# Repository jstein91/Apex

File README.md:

# Apex
 APEX KEYBOARD

TKL keyboard with OLED, USB-C, USB hub and encoder.

## Inspiration

I thought of this board as a way to get all the features I want in a keyboard (encoders, OLED, USB hub) but with a design I can evolve with the times and add features to as my skills and knowledge increase. At its core, I intend for it to be a daily driver that I will be able to use for many years and one that I can use and redesign as new tech comes out. The diging borrows heavily from the hub keyboard created by /konstantinwerner and has obvious inspiration from the ever-sought-after Satisfaction 75.

To that end, as a base design the keyboard utilizes the unified USB C daughter board designed by Acheron Project, has an OLED, a rotary encoder, and an integrated USB hub with 2 USB A ports. 

I know that this desgin isnt perfect. I plan to refine the key matrix. I also intend to implement various design changes in the future iterations such as:
 - RGB underglow
 - Per key backlighting
 - Design USB A daughterboard to make hub swappable between USB A and USB C
 - Possible bluetooth
 - Implement pogo pin for wireless communication between keyboard and seperate numpad(TBD) (much more research needed)

## Reference:

https://github.com/ruiqimao/keyboard-pcb-guide

http://blog.komar.be/how-to-make-a-keyboard-the-matrix/?source=post_page---------------------------

https://wiki.ai03.com/books/pcb-design

http://builder.swillkb.com/

## Resources:

https://github.com/CaninoDev/MechanicalKeyboardKiCADTemplates

https://github.com/konstantinwerner/hub_keyboard

https://github.com/BenRoe/awesome-mechanical-keyboard

https://github.com/di0ib/Misc

https://github.com/CaninoDev/MechanicalKeyboardKiCADTemplates

http://ww1.microchip.com/downloads/en/DeviceDoc/doc7593.pdf

https://kb.xyz.is/

https://builder.mrkeebs.com/

https://github.com/adamws/kicad-kbplacer

https://github.com/AcheronProject

https://github.com/ai03-2725/Unified-Daughterboard

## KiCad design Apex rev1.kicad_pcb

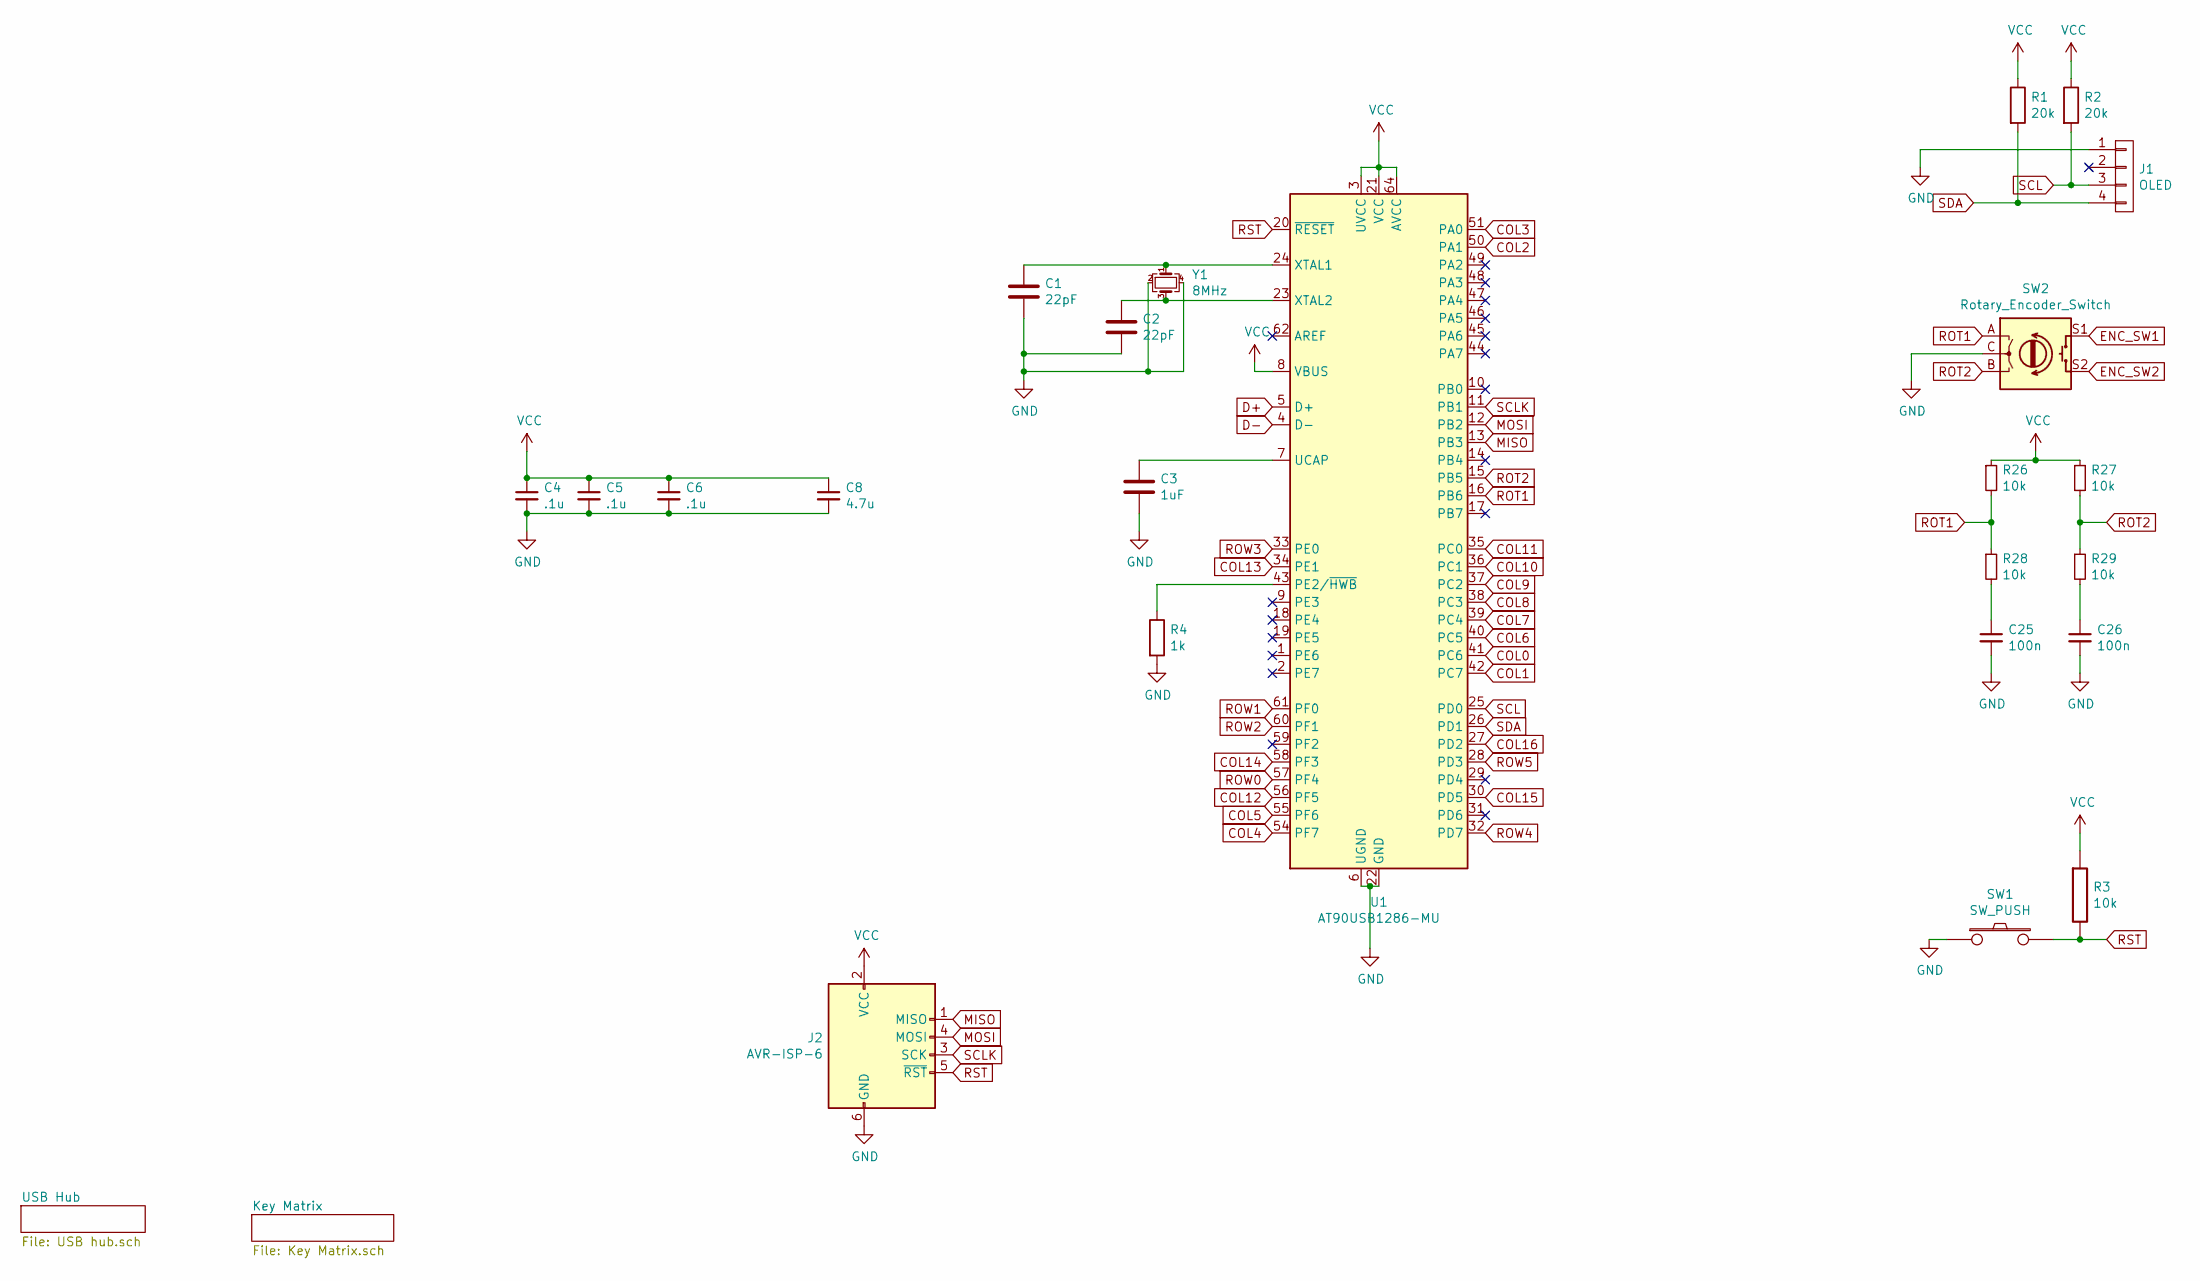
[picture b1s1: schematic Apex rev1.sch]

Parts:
C1, C2: 22pF; C_0805_2012Metric
C3: 1uF; C_0805_2012Metric
C4, C5, C6: .1u; C_0805_2012Metric
C8: 4.7u; C_0805_2012Metric
C25, C26: 100n; C_0805_2012Metric
J1: OLED; 128X32_I2C_OLED
J2: AVR-ISP-6; ICSP-Header
R1, R2: 20k; R_0603
R3, R26, R27, R28, R29: 10k; R_0603
R4: 1k; R_0603
SW1: SW_PUSH; SKQG-1155865
SW2: Rotary_Encoder_Switch; RotaryEncoder_EC11
U1: AT90USB1286-MU; QFN-64-1EP_9x9mm_P0.5mm_EP7.5x7.5mm
Y1: 8MHz; Crystal_SMD_3225-4Pin_3.2x2.5mm

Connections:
COL0: U1.41 (PC6); also elsewhere on the board
COL1: U1.42 (PC7); also elsewhere on the board
COL2: U1.50 (PA1); also elsewhere on the board
COL3: U1.51 (PA0); also elsewhere on the board
COL4: U1.54 (PF7); also elsewhere on the board
COL5: U1.55 (PF6); also elsewhere on the board
COL6: U1.40 (PC5); also elsewhere on the board
COL7: U1.39 (PC4); also elsewhere on the board
COL8: U1.38 (PC3); also elsewhere on the board
COL9: U1.37 (PC2); also elsewhere on the board
COL10: U1.36 (PC1); also elsewhere on the board
COL11: U1.35 (PC0); also elsewhere on the board
COL12: U1.56 (PF5); also elsewhere on the board
COL13: U1.34 (PE1); also elsewhere on the board
COL14: U1.58 (PF3); also elsewhere on the board
COL15: U1.30 (PD5); also elsewhere on the board
COL16: U1.27 (PD2); also elsewhere on the board
D+: U1.5 (D+); also elsewhere on the board
D-: U1.4 (D-); also elsewhere on the board
ENC_SW1: SW2.S1
ENC_SW2: SW2.S2
GND: C1.2, C2.2, C3.2, C4.2, C5.2, C6.2, C8.2, C25.2, C26.2, J1.1, J2.6 (GND), R4.2, SW1.1, SW2.C, U1.6 (UGND), U1.22 (GND), U1.53 (GND), U1.63 (GND), U1.65 (GND), Y1.2, Y1.4; also elsewhere on the board
MISO: J2.1 (MISO), U1.13 (PB3)
MOSI: J2.4 (MOSI), U1.12 (PB2)
unnamed: C1.1, U1.24 (XTAL1), Y1.1
unnamed: C2.1, U1.23 (XTAL2), Y1.3
unnamed: C3.1, U1.7 (UCAP)
unnamed: C25.1, R28.2
unnamed: C26.1, R29.2
unnamed: R4.1, U1.43 (PE2/~HWB)
ROT1: R26.2, R28.1, SW2.A, U1.16 (PB6)
ROT2: R27.2, R29.1, SW2.B, U1.15 (PB5)
ROW0: U1.57 (PF4); also elsewhere on the board
ROW1: U1.61 (PF0); also elsewhere on the board
ROW2: U1.60 (PF1); also elsewhere on the board
ROW3: U1.33 (PE0); also elsewhere on the board
ROW4: U1.32 (PD7); also elsewhere on the board
ROW5: U1.28 (PD3); also elsewhere on the board
RST: J2.5 (~RST), R3.2, SW1.2, U1.20 (~RESET)
SCL: J1.3, R2.2, U1.25 (PD0)
SCLK: J2.3 (SCK), U1.11 (PB1)
SDA: J1.4, R1.2, U1.26 (PD1)
VCC: C4.1, C5.1, C6.1, C8.1, J2.2 (VCC), R1.1, R2.1, R3.1, R26.1, R27.1, U1.3 (UVCC), U1.8 (VBUS), U1.21 (VCC), U1.52 (VCC), U1.64 (AVCC); also elsewhere on the board

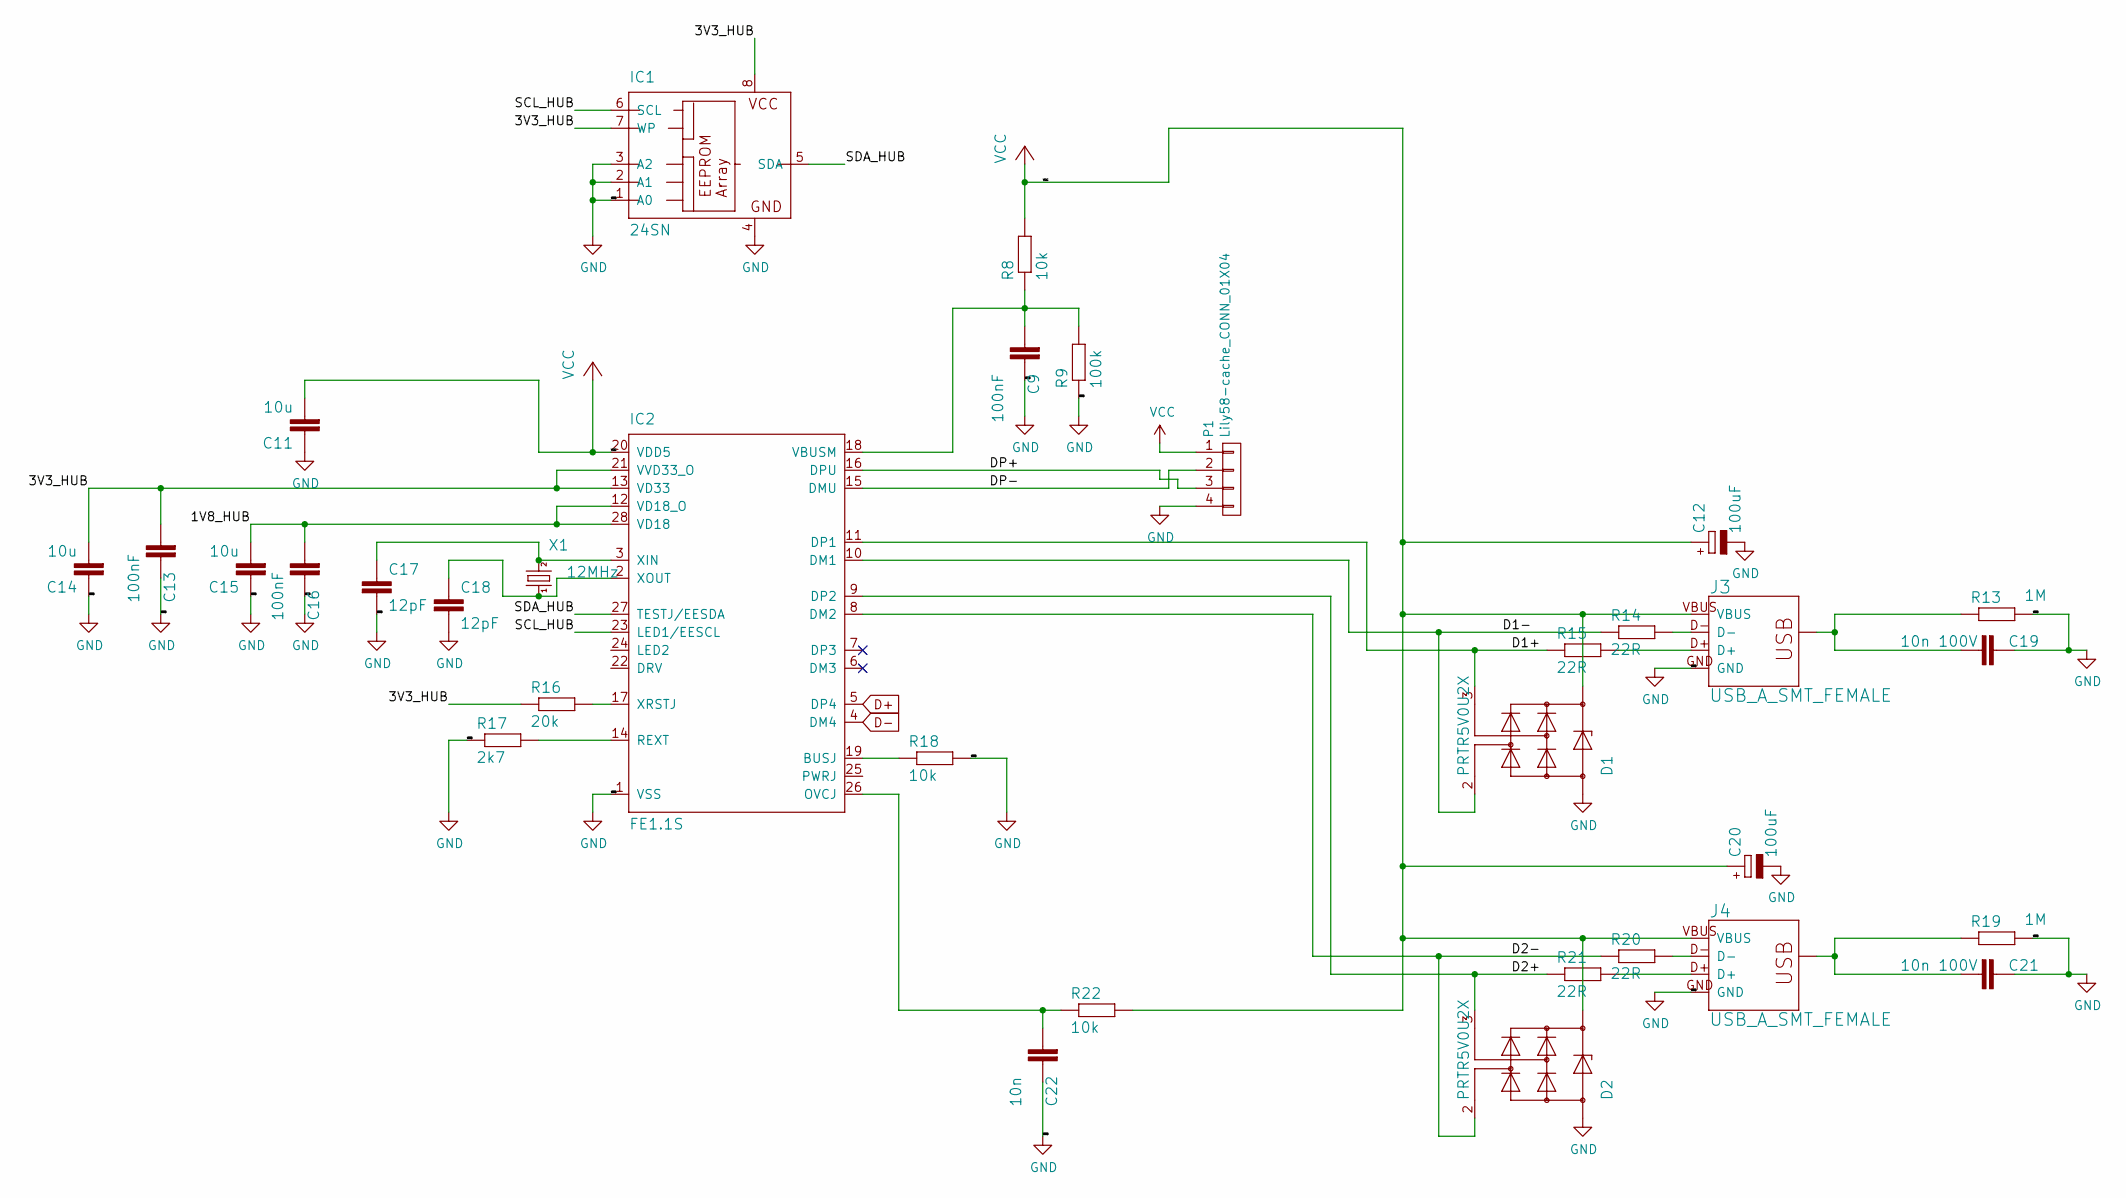
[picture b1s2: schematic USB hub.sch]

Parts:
C9, C13, C16: 100nF; C_0805_2012Metric; LCSC C14663
C11, C14, C15: 10u; C_0805_2012Metric; LCSC C19702
C12, C20: 100uF; CT3528; LCSC C16133
C17, C18: 12pF; C_0805_2012Metric; LCSC C38523
C19, C21: 10n 100V; C_0805_2012Metric; LCSC C84709
C22: 10n; C_0805_2012Metric; LCSC C57112
D1, D2: PRTR5V0U2X; SOT143; DIGIKEY 1727-3884-1-ND
IC1: 24SN; SO-08; LCSC C184083
IC2: FE1.1S; SSOP28; LCSC C9359
J3, J4: USB_A_SMT_FEMALE; USB-A-S-SILK-FEMALE; DIGIKEY 609-4946-1-ND
P1: Lily58-cache_CONN_01X04; JST-SR-4
R8, R18, R22: 10k; R_0603; LCSC C25804
R9: 100k; R_0603; LCSC C25803
R13, R19: 1M; R_0603; LCSC C22935
R14, R15, R20, R21: 22R; R_0603; LCSC C23345
R16: 20k; R_0603; LCSC C4184
R17: 2k7; R_0603; LCSC C13167
X1: 12MHz; Crystal_SMD_3225-4Pin_3.2x2.5mm; LCSC C9002

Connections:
/USB Hub/1V8_HUB: C15.2, C16.2, IC2.12 (VD18_O), IC2.28 (VD18)
/USB Hub/3V3_HUB: C13.2, C14.2, IC1.7 (WP), IC1.8 (VCC), IC2.13 (VD33), IC2.21 (VVD33_O), R16.1
/USB Hub/D1+: D1.3 (IO2), IC2.11 (DP1), R15.1
/USB Hub/D1-: D1.2 (IO1), IC2.10 (DM1), R14.1
/USB Hub/D2+: D2.3 (IO2), IC2.9 (DP2), R21.1
/USB Hub/D2-: D2.2 (IO1), IC2.8 (DM2), R20.1
/USB Hub/DP+: IC2.16 (DPU), P1.3
/USB Hub/DP-: IC2.15 (DMU), P1.2
/USB Hub/SCL_HUB: IC1.6 (SCL), IC2.23 (LED1/EESCL)
/USB Hub/SDA_HUB: IC1.5 (SDA), IC2.27 (TESTJ/EESDA)
D+: IC2.5 (DP4); also elsewhere on the board
D-: IC2.4 (DM4); also elsewhere on the board
GND: C9.1, C11.1, C12.-, C13.1, C14.1, C15.1, C16.1, C17.2, C18.2, C19.1, C20.-, C21.1, C22.1, D1.1 (GND), D2.1 (GND), IC1.1 (A0), IC1.2 (A1), IC1.3 (A2), IC1.4 (GND), IC2.1 (VSS), J3.GND, J4.GND, P1.4, R9.1, R13.2, R17.1, R18.2, R19.2; also elsewhere on the board
unnamed: C9.2, IC2.18 (VBUSM), R8.1, R9.2
unnamed: C17.1, IC2.3 (XIN), X1.3 (2)
unnamed: C18.1, IC2.2 (XOUT), X1.1
unnamed: C19.2, J3.SHLD1 (SHIELD), J3.SHLD2 (SHIELD), R13.1
unnamed: C21.2, J4.SHLD1 (SHIELD), J4.SHLD2 (SHIELD), R19.1
unnamed: C22.2, IC2.26 (OVCJ), R22.1
unnamed: IC2.14 (REXT), R17.2
unnamed: IC2.17 (XRSTJ), R16.2
unnamed: IC2.19 (BUSJ), R18.1
unnamed: J3.D+, R15.2
unnamed: J3.D-, R14.2
unnamed: J4.D+, R21.2
unnamed: J4.D-, R20.2
VCC: C11.2, C12.+, C20.+, D1.4 (VCC), D2.4 (VCC), IC2.20 (VDD5), J3.VBUS, J4.VBUS, P1.1, R8.2, R22.2; also elsewhere on the board

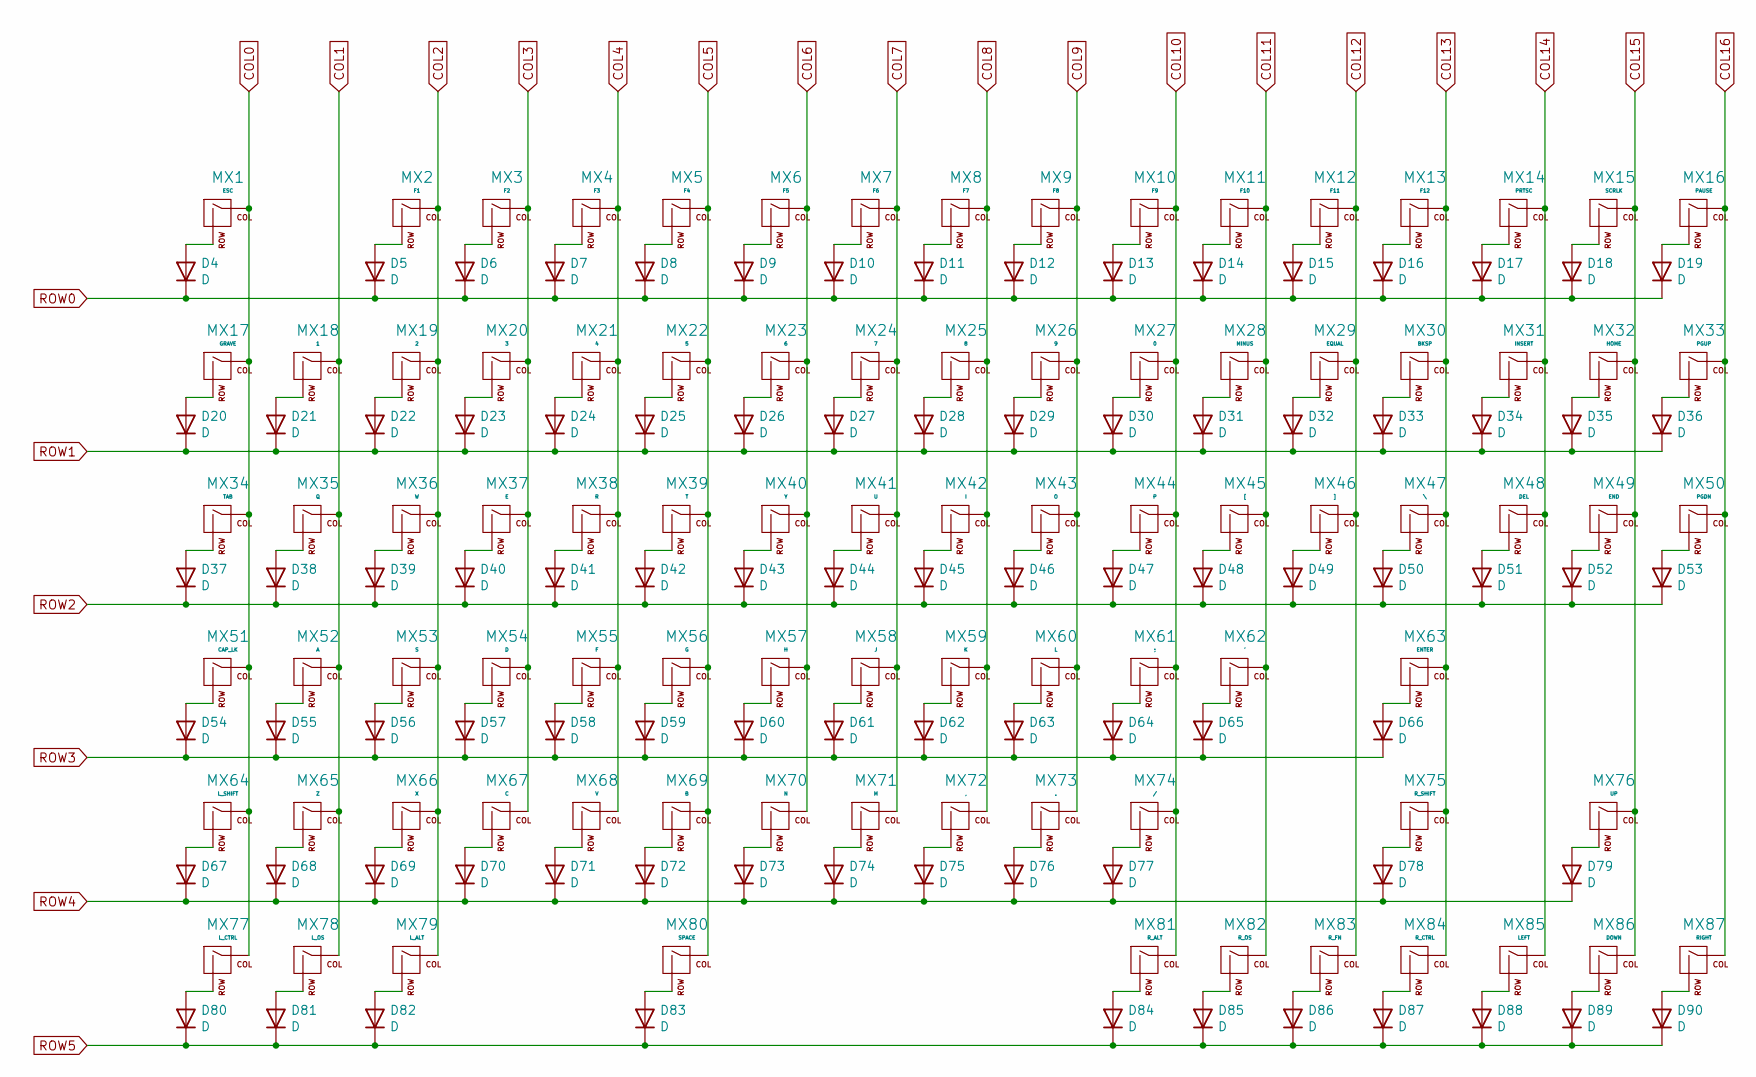
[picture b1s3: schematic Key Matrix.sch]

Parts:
D4, D5, D6, D7, D8, D9, D10, D11, D12, D13, D14, D15, D16, D17, D18, D19, D20, D21, D22, D23, D24, D25, D26, D27, D28, D29, D30, D31, D32, D33, D34, D35, D36, D37, D38, D39, D40, D41, D42, D43, D44, D45, D46, D47, D48, D49, D50, D51, D52, D53, D54, D55, D56, D57, D58, D59, D60, D61, D62, D63, D64, D65, D66, D67, D68, D69, D70, D71, D72, D73, D74, D75, D76, D77, D78, D79, D80, D81, D82, D83, D84, D85, D86, D87, D88, D89, D90: D; D_SOD-123
MX1: ESC; MXOnly-1U-NoLED
MX2: F1; MXOnly-1U-NoLED
MX3: F2; MXOnly-1U-NoLED
MX4: F3; MXOnly-1U-NoLED
MX5: F4; MXOnly-1U-NoLED
MX6: F5; MXOnly-1U-NoLED
MX7: F6; MXOnly-1U-NoLED
MX8: F7; MXOnly-1U-NoLED
MX9: F8; MXOnly-1U-NoLED
MX10: F9; MXOnly-1U-NoLED
MX11: F10; MXOnly-1U-NoLED
MX12: F11; MXOnly-1U-NoLED
MX13: F12; MXOnly-1U-NoLED
MX14: PRTSC; MXOnly-1U-NoLED
MX15: SCRLK; MXOnly-1U-NoLED
MX16: PAUSE; MXOnly-1U-NoLED
MX17: GRAVE; MXOnly-1U-NoLED
MX18: 1; MXOnly-1U-NoLED
MX19: 2; MXOnly-1U-NoLED
MX20: 3; MXOnly-1U-NoLED
MX21: 4; MXOnly-1U-NoLED
MX22: 5; MXOnly-1U-NoLED
MX23: 6; MXOnly-1U-NoLED
MX24: 7; MXOnly-1U-NoLED
MX25: 8; MXOnly-1U-NoLED
MX26: 9; MXOnly-1U-NoLED
MX27: 0; MXOnly-1U-NoLED
MX28: MINUS; MXOnly-1U-NoLED
MX29: EQUAL; MXOnly-1U-NoLED
MX30: BKSP; MXOnly-2U-NoLED
MX31: INSERT; MXOnly-1U-NoLED
MX32: HOME; MXOnly-1U-NoLED
MX33: PGUP; MXOnly-1U-NoLED
MX34: TAB; MXOnly-1.5U-NoLED
MX35: Q; MXOnly-1U-NoLED
MX36: W; MXOnly-1U-NoLED
MX37: E; MXOnly-1U-NoLED
MX38: R; MXOnly-1U-NoLED
MX39: T; MXOnly-1U-NoLED
MX40: Y; MXOnly-1U-NoLED
MX41: U; MXOnly-1U-NoLED
MX42: I; MXOnly-1U-NoLED
MX43: O; MXOnly-1U-NoLED
MX44: P; MXOnly-1U-NoLED
MX45: [; MXOnly-1U-NoLED
MX46: ]; MXOnly-1U-NoLED
MX47: \\; MXOnly-1.5U-NoLED
MX48: DEL; MXOnly-1U-NoLED
MX49: END; MXOnly-1U-NoLED
MX50: PGDN; MXOnly-1U-NoLED
MX51: CAP_LK; MXOnly-1.75U-NoLED
MX52: A; MXOnly-1U-NoLED
MX53: S; MXOnly-1U-NoLED
MX54: D; MXOnly-1U-NoLED
MX55: F; MXOnly-1U-NoLED
MX56: G; MXOnly-1U-NoLED
MX57: H; MXOnly-1U-NoLED
MX58: J; MXOnly-1U-NoLED
MX59: K; MXOnly-1U-NoLED
MX60: L; MXOnly-1U-NoLED
MX61: ;; MXOnly-1U-NoLED
MX62: '; MXOnly-1U-NoLED
MX63: ENTER; MXOnly-2.25U-NoLED
MX64: L_SHIFT; MXOnly-2.25U-NoLED
MX65: Z; MXOnly-1U-NoLED
MX66: X; MXOnly-1U-NoLED
MX67: C; MXOnly-1U-NoLED
MX68: V; MXOnly-1U-NoLED
MX69: B; MXOnly-1U-NoLED
MX70: N; MXOnly-1U-NoLED
MX71: M; MXOnly-1U-NoLED
MX72: ,; MXOnly-1U-NoLED
MX73: .; MXOnly-1U-NoLED
MX74: /; MXOnly-1U-NoLED
MX75: R_SHIFT; MXOnly-2.75U-NoLED
MX76: UP; MXOnly-1U-NoLED
MX77: L_CTRL; MXOnly-1.25U-NoLED
MX78: L_OS; MXOnly-1.25U-NoLED
MX79: L_ALT; MXOnly-1.25U-NoLED
MX80: SPACE; MXOnly-6.25U-NoLED
MX81: R_ALT; MXOnly-1.75U-NoLED
MX82: R_OS; MXOnly-1.25U-NoLED
MX83: R_FN; MXOnly-1.25U-NoLED
MX84: R_CTRL; MXOnly-1.25U-NoLED
MX85: LEFT; MXOnly-1U-NoLED
MX86: DOWN; MXOnly-1U-NoLED
MX87: RIGHT; MXOnly-1U-NoLED

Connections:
COL0: MX1.1 (COL), MX17.1 (COL), MX34.1 (COL), MX51.1 (COL), MX64.1 (COL), MX77.1 (COL); also elsewhere on the board
COL1: MX18.1 (COL), MX35.1 (COL), MX52.1 (COL), MX65.1 (COL), MX78.1 (COL); also elsewhere on the board
COL2: MX2.1 (COL), MX19.1 (COL), MX36.1 (COL), MX53.1 (COL), MX66.1 (COL), MX79.1 (COL); also elsewhere on the board
COL3: MX3.1 (COL), MX20.1 (COL), MX37.1 (COL), MX54.1 (COL), MX67.1 (COL); also elsewhere on the board
COL4: MX4.1 (COL), MX21.1 (COL), MX38.1 (COL), MX55.1 (COL), MX68.1 (COL); also elsewhere on the board
COL5: MX5.1 (COL), MX22.1 (COL), MX39.1 (COL), MX56.1 (COL), MX69.1 (COL), MX80.1 (COL); also elsewhere on the board
COL6: MX6.1 (COL), MX23.1 (COL), MX40.1 (COL), MX57.1 (COL), MX70.1 (COL); also elsewhere on the board
COL7: MX7.1 (COL), MX24.1 (COL), MX41.1 (COL), MX58.1 (COL), MX71.1 (COL); also elsewhere on the board
COL8: MX8.1 (COL), MX25.1 (COL), MX42.1 (COL), MX59.1 (COL), MX72.1 (COL); also elsewhere on the board
COL9: MX9.1 (COL), MX26.1 (COL), MX43.1 (COL), MX60.1 (COL), MX73.1 (COL); also elsewhere on the board
COL10: MX10.1 (COL), MX27.1 (COL), MX44.1 (COL), MX61.1 (COL), MX74.1 (COL), MX81.1 (COL); also elsewhere on the board
COL11: MX11.1 (COL), MX28.1 (COL), MX45.1 (COL), MX62.1 (COL), MX82.1 (COL); also elsewhere on the board
COL12: MX12.1 (COL), MX29.1 (COL), MX46.1 (COL), MX83.1 (COL); also elsewhere on the board
COL13: MX13.1 (COL), MX30.1 (COL), MX47.1 (COL), MX63.1 (COL), MX75.1 (COL), MX84.1 (COL); also elsewhere on the board
COL14: MX14.1 (COL), MX31.1 (COL), MX48.1 (COL), MX85.1 (COL); also elsewhere on the board
COL15: MX15.1 (COL), MX32.1 (COL), MX49.1 (COL), MX76.1 (COL), MX86.1 (COL); also elsewhere on the board
COL16: MX16.1 (COL), MX33.1 (COL), MX50.1 (COL), MX87.1 (COL); also elsewhere on the board
unnamed: D4.2 (A), MX1.2 (ROW)
unnamed: D5.2 (A), MX2.2 (ROW)
unnamed: D6.2 (A), MX3.2 (ROW)
unnamed: D7.2 (A), MX4.2 (ROW)
unnamed: D8.2 (A), MX5.2 (ROW)
unnamed: D9.2 (A), MX6.2 (ROW)
unnamed: D10.2 (A), MX7.2 (ROW)
unnamed: D11.2 (A), MX8.2 (ROW)
unnamed: D12.2 (A), MX9.2 (ROW)
unnamed: D13.2 (A), MX10.2 (ROW)
unnamed: D14.2 (A), MX11.2 (ROW)
unnamed: D15.2 (A), MX12.2 (ROW)
unnamed: D16.2 (A), MX13.2 (ROW)
unnamed: D17.2 (A), MX14.2 (ROW)
unnamed: D18.2 (A), MX15.2 (ROW)
unnamed: D19.2 (A), MX16.2 (ROW)
unnamed: D20.2 (A), MX17.2 (ROW)
unnamed: D21.2 (A), MX18.2 (ROW)
unnamed: D22.2 (A), MX19.2 (ROW)
unnamed: D23.2 (A), MX20.2 (ROW)
unnamed: D24.2 (A), MX21.2 (ROW)
unnamed: D25.2 (A), MX22.2 (ROW)
unnamed: D26.2 (A), MX23.2 (ROW)
unnamed: D27.2 (A), MX24.2 (ROW)
unnamed: D28.2 (A), MX25.2 (ROW)
unnamed: D29.2 (A), MX26.2 (ROW)
unnamed: D30.2 (A), MX27.2 (ROW)
unnamed: D31.2 (A), MX28.2 (ROW)
unnamed: D32.2 (A), MX29.2 (ROW)
unnamed: D33.2 (A), MX30.2 (ROW)
unnamed: D34.2 (A), MX31.2 (ROW)
unnamed: D35.2 (A), MX32.2 (ROW)
unnamed: D36.2 (A), MX33.2 (ROW)
unnamed: D37.2 (A), MX34.2 (ROW)
unnamed: D38.2 (A), MX35.2 (ROW)
unnamed: D39.2 (A), MX36.2 (ROW)
unnamed: D40.2 (A), MX37.2 (ROW)
unnamed: D41.2 (A), MX38.2 (ROW)
unnamed: D42.2 (A), MX39.2 (ROW)
unnamed: D43.2 (A), MX40.2 (ROW)
unnamed: D44.2 (A), MX41.2 (ROW)
unnamed: D45.2 (A), MX42.2 (ROW)
unnamed: D46.2 (A), MX43.2 (ROW)
unnamed: D47.2 (A), MX44.2 (ROW)
unnamed: D48.2 (A), MX45.2 (ROW)
unnamed: D49.2 (A), MX46.2 (ROW)
unnamed: D50.2 (A), MX47.2 (ROW)
unnamed: D51.2 (A), MX48.2 (ROW)
unnamed: D52.2 (A), MX49.2 (ROW)
unnamed: D53.2 (A), MX50.2 (ROW)
unnamed: D54.2 (A), MX51.2 (ROW)
unnamed: D55.2 (A), MX52.2 (ROW)
unnamed: D56.2 (A), MX53.2 (ROW)
unnamed: D57.2 (A), MX54.2 (ROW)
unnamed: D58.2 (A), MX55.2 (ROW)
unnamed: D59.2 (A), MX56.2 (ROW)
unnamed: D60.2 (A), MX57.2 (ROW)
unnamed: D61.2 (A), MX58.2 (ROW)
unnamed: D62.2 (A), MX59.2 (ROW)
unnamed: D63.2 (A), MX60.2 (ROW)
unnamed: D64.2 (A), MX61.2 (ROW)
unnamed: D65.2 (A), MX62.2 (ROW)
unnamed: D66.2 (A), MX63.2 (ROW)
unnamed: D67.2 (A), MX64.2 (ROW)
unnamed: D68.2 (A), MX65.2 (ROW)
unnamed: D69.2 (A), MX66.2 (ROW)
unnamed: D70.2 (A), MX67.2 (ROW)
unnamed: D71.2 (A), MX68.2 (ROW)
unnamed: D72.2 (A), MX69.2 (ROW)
unnamed: D73.2 (A), MX70.2 (ROW)
unnamed: D74.2 (A), MX71.2 (ROW)
unnamed: D75.2 (A), MX72.2 (ROW)
unnamed: D76.2 (A), MX73.2 (ROW)
unnamed: D77.2 (A), MX74.2 (ROW)
unnamed: D78.2 (A), MX75.2 (ROW)
unnamed: D79.2 (A), MX76.2 (ROW)
unnamed: D80.2 (A), MX77.2 (ROW)
unnamed: D81.2 (A), MX78.2 (ROW)
unnamed: D82.2 (A), MX79.2 (ROW)
unnamed: D83.2 (A), MX80.2 (ROW)
unnamed: D84.2 (A), MX81.2 (ROW)
unnamed: D85.2 (A), MX82.2 (ROW)
unnamed: D86.2 (A), MX83.2 (ROW)
unnamed: D87.2 (A), MX84.2 (ROW)
unnamed: D88.2 (A), MX85.2 (ROW)
unnamed: D89.2 (A), MX86.2 (ROW)
unnamed: D90.2 (A), MX87.2 (ROW)
ROW0: D4.1 (K), D5.1 (K), D6.1 (K), D7.1 (K), D8.1 (K), D9.1 (K), D10.1 (K), D11.1 (K), D12.1 (K), D13.1 (K), D14.1 (K), D15.1 (K), D16.1 (K), D17.1 (K), D18.1 (K), D19.1 (K); also elsewhere on the board
ROW1: D20.1 (K), D21.1 (K), D22.1 (K), D23.1 (K), D24.1 (K), D25.1 (K), D26.1 (K), D27.1 (K), D28.1 (K), D29.1 (K), D30.1 (K), D31.1 (K), D32.1 (K), D33.1 (K), D34.1 (K), D35.1 (K), D36.1 (K); also elsewhere on the board
ROW2: D37.1 (K), D38.1 (K), D39.1 (K), D40.1 (K), D41.1 (K), D42.1 (K), D43.1 (K), D44.1 (K), D45.1 (K), D46.1 (K), D47.1 (K), D48.1 (K), D49.1 (K), D50.1 (K), D51.1 (K), D52.1 (K), D53.1 (K); also elsewhere on the board
ROW3: D54.1 (K), D55.1 (K), D56.1 (K), D57.1 (K), D58.1 (K), D59.1 (K), D60.1 (K), D61.1 (K), D62.1 (K), D63.1 (K), D64.1 (K), D65.1 (K), D66.1 (K); also elsewhere on the board
ROW4: D67.1 (K), D68.1 (K), D69.1 (K), D70.1 (K), D71.1 (K), D72.1 (K), D73.1 (K), D74.1 (K), D75.1 (K), D76.1 (K), D77.1 (K), D78.1 (K), D79.1 (K); also elsewhere on the board
ROW5: D80.1 (K), D81.1 (K), D82.1 (K), D83.1 (K), D84.1 (K), D85.1 (K), D86.1 (K), D87.1 (K), D88.1 (K), D89.1 (K), D90.1 (K); also elsewhere on the board

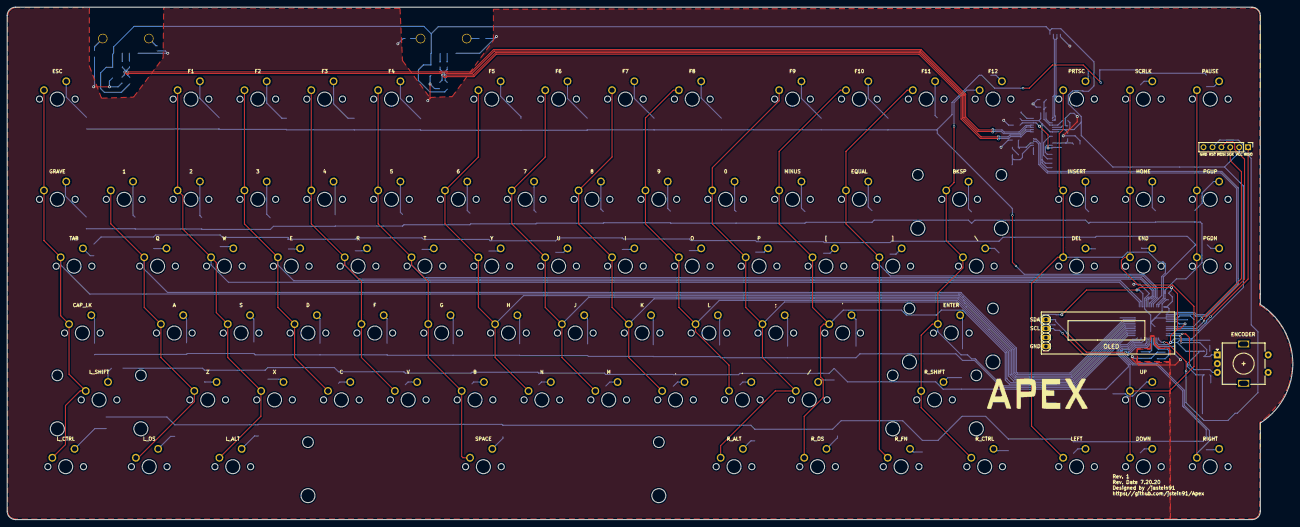
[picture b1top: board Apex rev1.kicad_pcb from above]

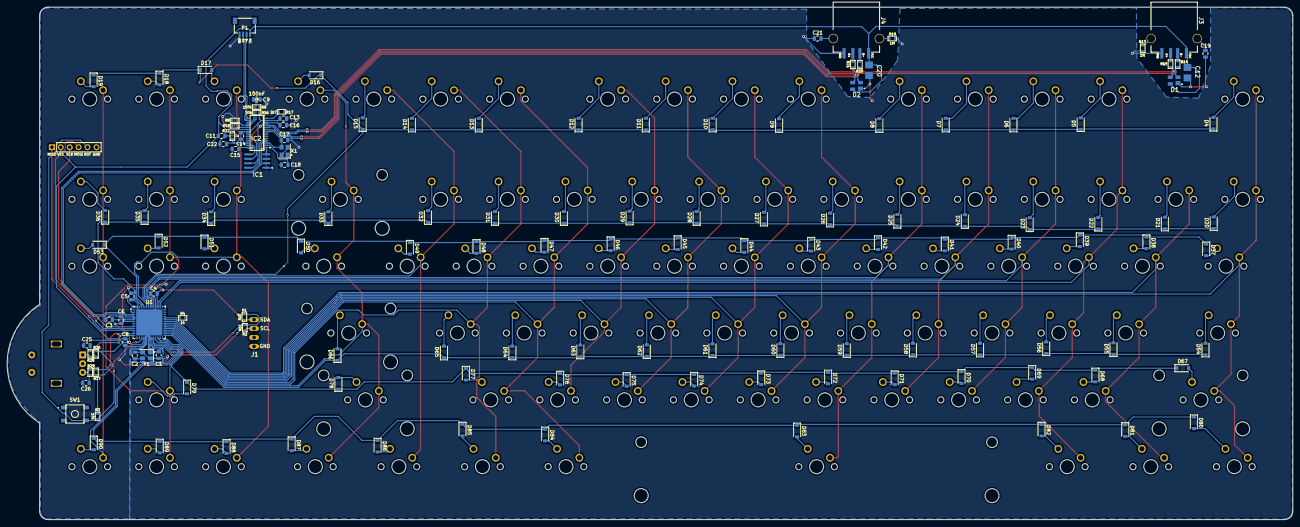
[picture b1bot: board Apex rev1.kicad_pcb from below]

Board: 2 copper layers, 366.4 x 146.1 mm, 230 parts (140 on the bottom side), 151 nets.

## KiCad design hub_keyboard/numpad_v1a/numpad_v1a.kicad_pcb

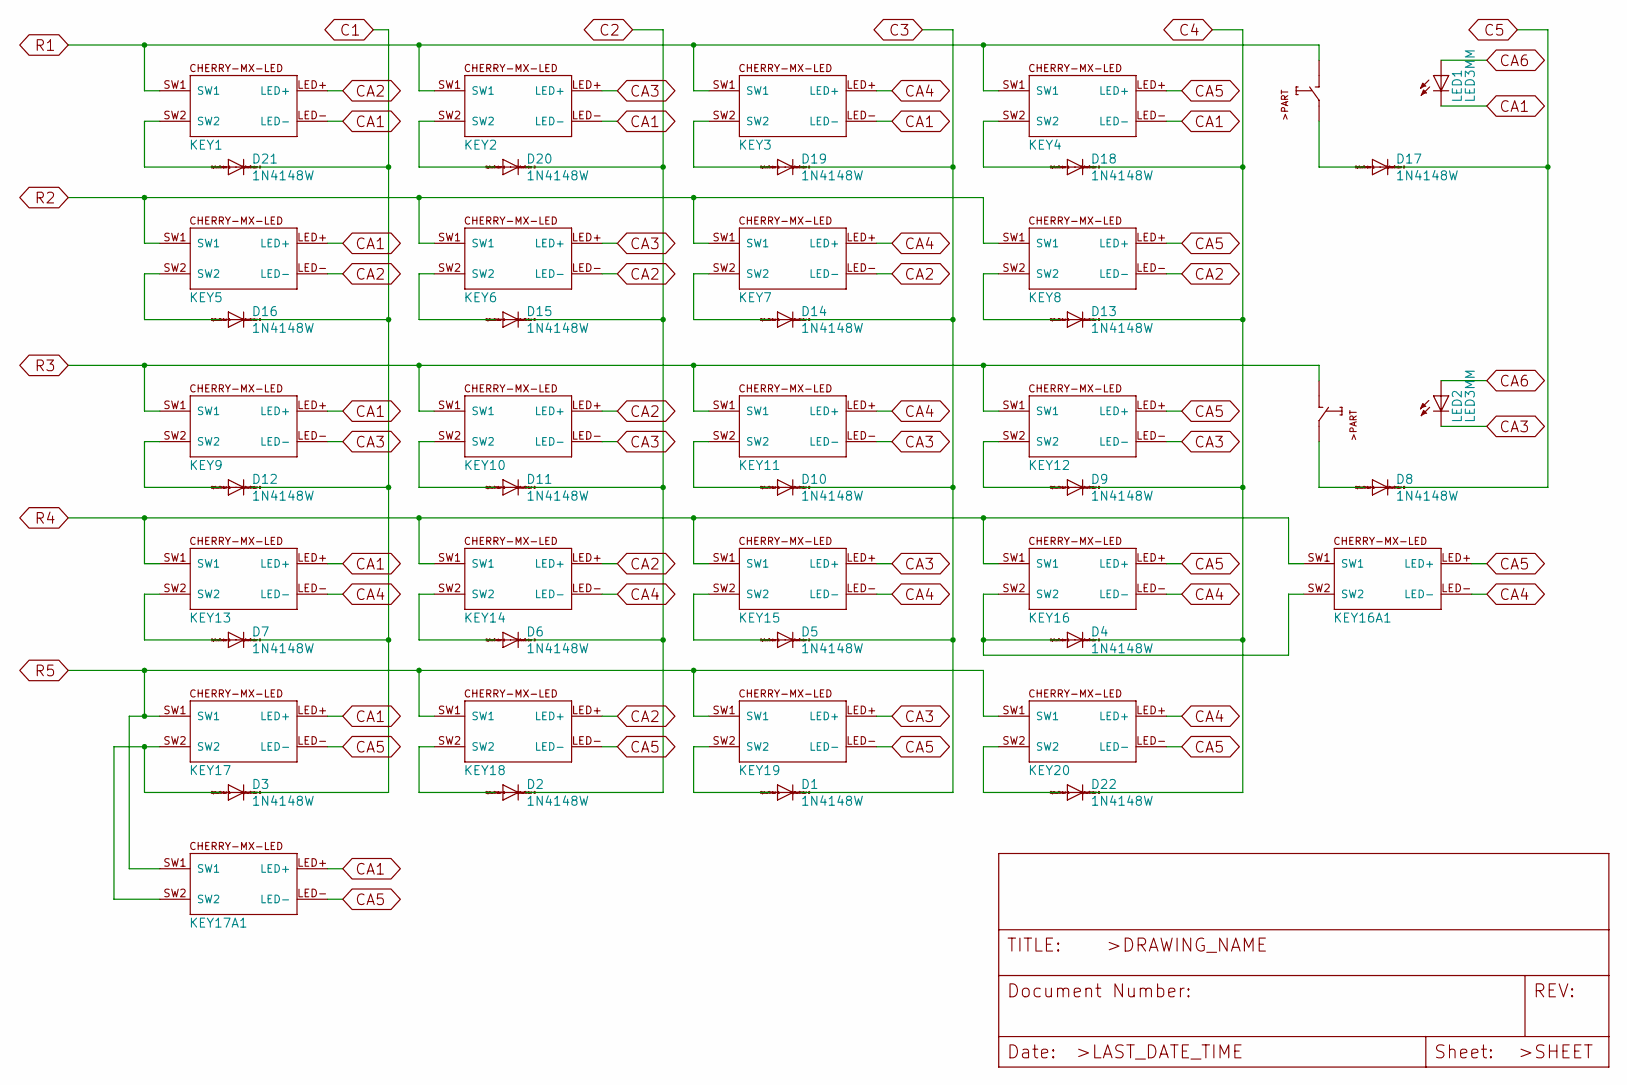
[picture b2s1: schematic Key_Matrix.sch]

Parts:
D1, D2, D3, D4, D5, D6, D7, D8, D9, D10, D11, D12, D13, D14, D15, D16, D17, D18, D19, D20, D21, D22: 1N4148W; SOD123; LCSC C81598
ENC1, ENC2: EC12E_SW; ALPS_EC12E_SW
KEY1, KEY2, KEY3, KEY4, KEY5, KEY6, KEY7, KEY8, KEY9, KEY10, KEY11, KEY12, KEY13, KEY14, KEY15, KEY16A, KEY17, KEY18, KEY19, KEY20: CHERRY-MX-LED
KEY16, KEY17A: CHERRY-MX-LED_NOHOLES
LED1, LED2: LED3MM

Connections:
C1: D3.C, D7.C, D12.C, D16.C, D21.C; also elsewhere on the board
C2: D2.C, D6.C, D11.C, D15.C, D20.C; also elsewhere on the board
C3: D1.C, D5.C, D10.C, D14.C, D19.C; also elsewhere on the board
C4: D4.C, D9.C, D13.C, D18.C, D22.C; also elsewhere on the board
C5: D8.C, D17.C; also elsewhere on the board
CA1: KEY1.LED-, KEY2.LED-, KEY3.LED-, KEY4.LED-, KEY5.LED+, KEY9.LED+, KEY13.LED+, KEY17.LED+, LED1.K (C); also elsewhere on the board
CA2: KEY1.LED+, KEY5.LED-, KEY6.LED-, KEY7.LED-, KEY8.LED-, KEY10.LED+, KEY14.LED+, KEY18.LED+; also elsewhere on the board
CA3: KEY2.LED+, KEY6.LED+, KEY9.LED-, KEY10.LED-, KEY11.LED-, KEY12.LED-, KEY15.LED+, KEY19.LED+, LED2.K (C); also elsewhere on the board
CA4: KEY3.LED+, KEY7.LED+, KEY11.LED+, KEY13.LED-, KEY14.LED-, KEY15.LED-, KEY16.LED-, KEY20.LED+; also elsewhere on the board
CA5: KEY4.LED+, KEY8.LED+, KEY12.LED+, KEY16.LED+, KEY17.LED-, KEY18.LED-, KEY19.LED-, KEY20.LED-; also elsewhere on the board
CA6: LED1.A, LED2.A; also elsewhere on the board
unnamed: D1.A, KEY19.SW2
unnamed: D2.A, KEY18.SW2
unnamed 33: D3.A, KEY17.SW2; also elsewhere on the board
unnamed 34: D4.A, KEY16.SW2; also elsewhere on the board
unnamed: D5.A, KEY15.SW2
unnamed: D6.A, KEY14.SW2
unnamed: D7.A, KEY13.SW2
unnamed: D8.A, ENC2.E (2)
unnamed: D9.A, KEY12.SW2
unnamed: D10.A, KEY11.SW2
unnamed: D11.A, KEY10.SW2
unnamed: D12.A, KEY9.SW2
unnamed: D13.A, KEY8.SW2
unnamed: D14.A, KEY7.SW2
unnamed: D15.A, KEY6.SW2
unnamed: D16.A, KEY5.SW2
unnamed: D17.A, ENC1.E (2)
unnamed: D18.A, KEY4.SW2
unnamed: D19.A, KEY3.SW2
unnamed: D20.A, KEY2.SW2
unnamed: D21.A, KEY1.SW2
unnamed: D22.A, KEY20.SW2
R1: ENC1.D (1), KEY1.SW1, KEY2.SW1, KEY3.SW1, KEY4.SW1; also elsewhere on the board
R2: KEY5.SW1, KEY6.SW1, KEY7.SW1, KEY8.SW1; also elsewhere on the board
R3: ENC2.D (1), KEY9.SW1, KEY10.SW1, KEY11.SW1, KEY12.SW1; also elsewhere on the board
R4: KEY13.SW1, KEY14.SW1, KEY15.SW1, KEY16.SW1; also elsewhere on the board
R5: KEY17.SW1, KEY18.SW1, KEY19.SW1, KEY20.SW1; also elsewhere on the board
